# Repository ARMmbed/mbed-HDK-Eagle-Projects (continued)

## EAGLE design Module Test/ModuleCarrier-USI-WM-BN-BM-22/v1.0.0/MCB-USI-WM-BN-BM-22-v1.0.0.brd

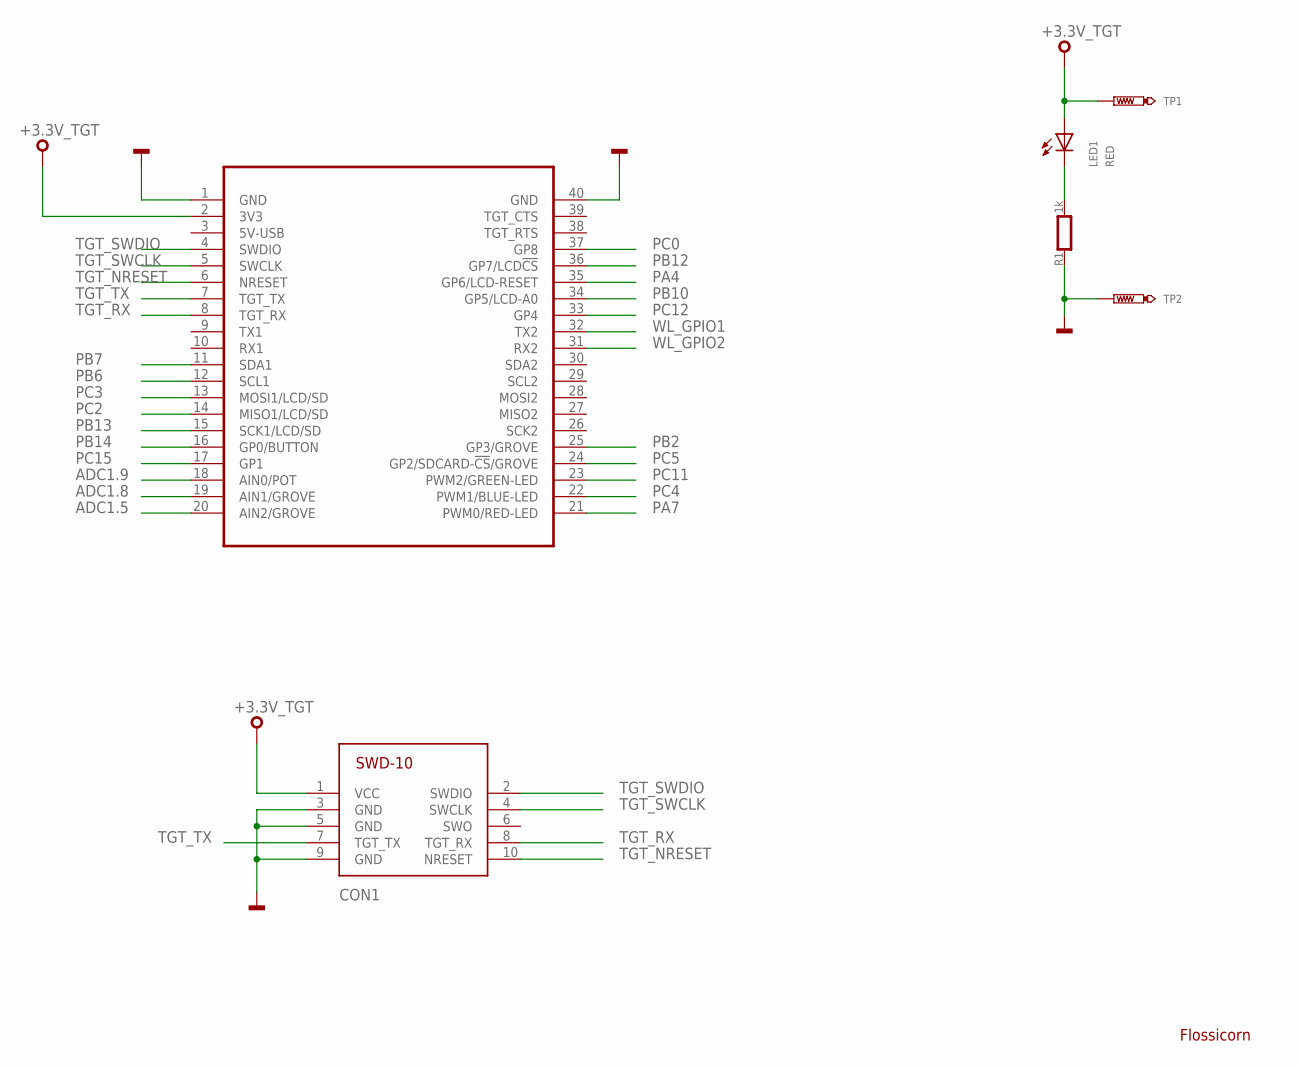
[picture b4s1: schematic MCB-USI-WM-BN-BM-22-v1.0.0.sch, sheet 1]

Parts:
CON1: SWD-10/TC2050_SMD; FTSH-105-02
LED1: RED; CHIPLED_0603
MOD1: MODULE_DAUGHTER
R1: 1k; 0603
SS1: FLOSSICORN0.5; FLOSSICORN-0.5
TP1, TP2: TEST-POINT-50R-PTH; TP50-PTH

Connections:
+3.3V_TGT: CON1.1 (VCC), LED1.A, MOD1.2 (3V3), TP1.TP; also elsewhere on the board
ADC1.5: MOD1.20 (AIN2/GROVE); also elsewhere on the board
ADC1.8: MOD1.19 (AIN1/GROVE); also elsewhere on the board
ADC1.9: MOD1.18 (AIN0/POT); also elsewhere on the board
GND: CON1.3 (GND), CON1.5 (GND), CON1.9 (GND), MOD1.1 (GND), MOD1.40 (GND), R1.1, TP2.TP; also elsewhere on the board
PA4: MOD1.35 (GP6/LCD-RESET); also elsewhere on the board
PA7: MOD1.21 (PWM0/RED-LED); also elsewhere on the board
PA_1: LED1.C, R1.2
PB2: MOD1.25 (GP3/GROVE); also elsewhere on the board
PB6: MOD1.12 (SCL1); also elsewhere on the board
PB7: MOD1.11 (SDA1); also elsewhere on the board
PB10: MOD1.34 (GP5/LCD-A0); also elsewhere on the board
PB12: MOD1.36 (GP7/LCD!CS); also elsewhere on the board
PB13: MOD1.15 (SCK1/LCD/SD); also elsewhere on the board
PB14: MOD1.16 (GP0/BUTTON); also elsewhere on the board
PC0: MOD1.37 (GP8); also elsewhere on the board
PC2: MOD1.14 (MISO1/LCD/SD); also elsewhere on the board
PC3: MOD1.13 (MOSI1/LCD/SD); also elsewhere on the board
PC4: MOD1.22 (PWM1/BLUE-LED); also elsewhere on the board
PC5: MOD1.24 (GP2/SDCARD-!CS!/GROVE); also elsewhere on the board
PC11: MOD1.23 (PWM2/GREEN-LED); also elsewhere on the board
PC12: MOD1.33 (GP4); also elsewhere on the board
PC15: MOD1.17 (GP1); also elsewhere on the board
TGT_NRESET: CON1.10 (NRESET), MOD1.6 (NRESET); also elsewhere on the board
TGT_RX: CON1.8 (TGT_RX), MOD1.8 (TGT_RX); also elsewhere on the board
TGT_SWCLK: CON1.4 (SWCLK), MOD1.5 (SWCLK); also elsewhere on the board
TGT_SWDIO: CON1.2 (SWDIO), MOD1.4 (SWDIO); also elsewhere on the board
TGT_TX: CON1.7 (TGT_TX), MOD1.7 (TGT_TX); also elsewhere on the board
WL_GPIO1: MOD1.32 (TX2); also elsewhere on the board
WL_GPIO2: MOD1.31 (RX2); also elsewhere on the board

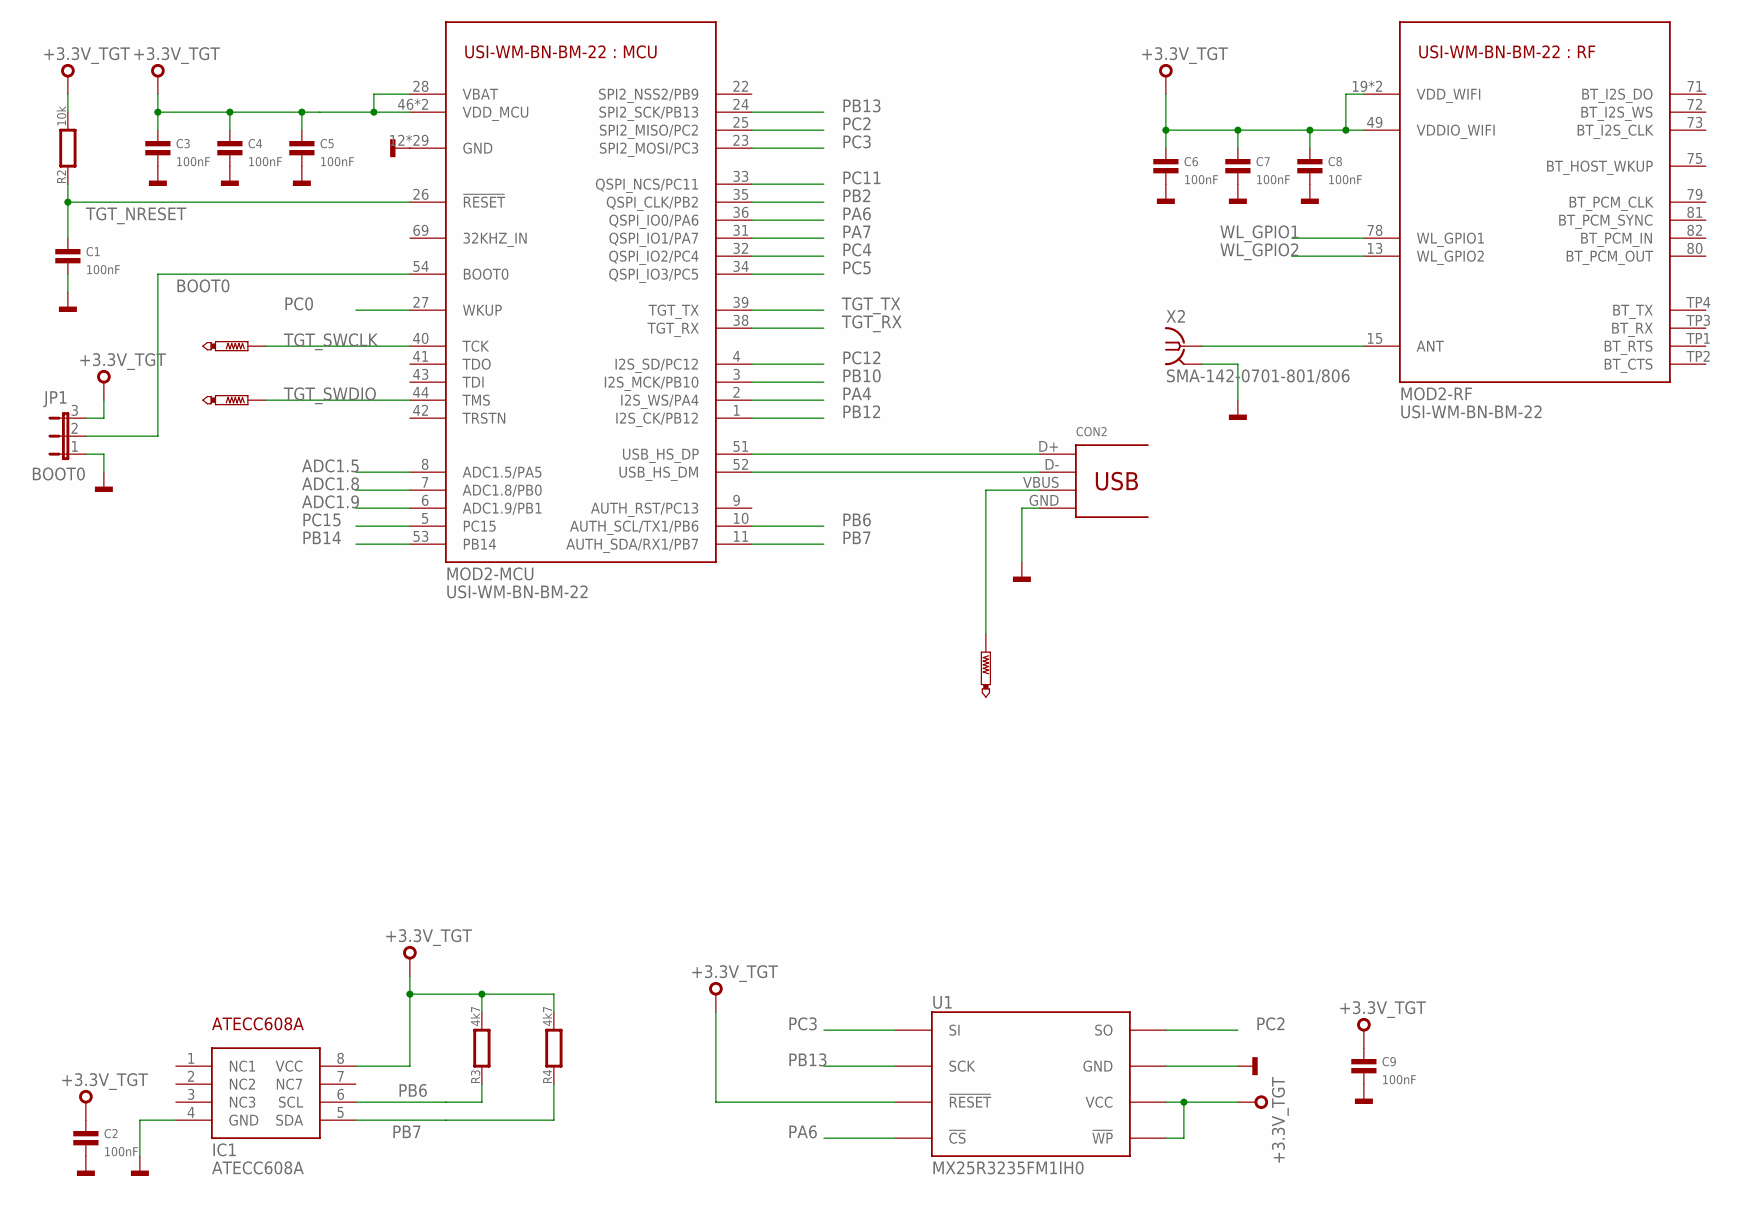
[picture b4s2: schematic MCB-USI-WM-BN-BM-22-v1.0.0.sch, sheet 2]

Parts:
C1, C2, C3, C4, C5, C6, C7, C8, C9: 100nF; 0603
CON2: 47346-0001; USB-MICRO-B-H
IC1: ATECC608A; SO8
JP1: BOOT0; JP2
MOD2: USI-WM-BN-BM-22
R2: 10k; 0603
R3, R4: 4k7; 0603
TP3, TP4: PTR1TP10R; TP10R
TP5: PTR1TP07R; TP07R
U1: MX25R3235FM1IH0; SO8
X2: SMA-142-0701-801/806; J502-ND-142-0701-801/806

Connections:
+3.3V_TGT: C2.1, C3.1, C4.1, C5.1, C6.1, C7.1, C8.1, C9.1, IC1.8 (VCC), JP1.3, MOD2.19 (VDD_WIFI), MOD2.20 (VDD_WIFI), MOD2.28 (VBAT), MOD2.46 (VDD_MCU), MOD2.47 (VDD_MCU), MOD2.49 (VDDIO_WIFI), R2.2, R3.2, R4.2, U1.3 (!WP), U1.7 (!RESET), U1.8 (VCC); also elsewhere on the board
ADC1.5: MOD2.8 (ADC1.5/PA5); also elsewhere on the board
ADC1.8: MOD2.7 (ADC1.8/PB0); also elsewhere on the board
ADC1.9: MOD2.6 (ADC1.9/PB1); also elsewhere on the board
BOOT0: JP1.2, MOD2.54 (BOOT0)
GND: C1.2, C2.2, C3.2, C4.2, C5.2, C6.2, C7.2, C8.2, C9.2, CON2.GND, IC1.4 (GND), JP1.1, MOD2.12 (GND), MOD2.14 (GND), MOD2.16 (GND), MOD2.17 (GND), MOD2.18 (GND), MOD2.21 (GND), MOD2.29 (GND), MOD2.30 (GND), MOD2.37 (GND), MOD2.45 (GND), MOD2.48 (GND), MOD2.50 (GND), MOD2.55 (GND), MOD2.56 (GND), MOD2.57 (GND), MOD2.58 (GND), MOD2.59 (GND), MOD2.60 (GND), MOD2.61 (GND), MOD2.62 (GND), MOD2.63 (GND), MOD2.64 (GND), MOD2.65 (GND), MOD2.66 (GND), MOD2.67 (GND), MOD2.68 (GND), MOD2.70 (GND), MOD2.74 (GND), MOD2.83 (GND), U1.4 (GND), X2.G@1 (2), X2.G@2 (2), X2.G@3 (2), X2.G@4 (2); also elsewhere on the board
unnamed: CON2.D+, MOD2.51 (USB_HS_DP)
unnamed: CON2.D-, MOD2.52 (USB_HS_DM)
unnamed: CON2.VBUS, TP5.TP
unnamed: MOD2.15 (ANT), X2.1
PA4: MOD2.2 (I2S_WS/PA4); also elsewhere on the board
PA6: MOD2.36 (QSPI_IO0/PA6), U1.1 (!CS)
PA7: MOD2.31 (QSPI_IO1/PA7); also elsewhere on the board
PB2: MOD2.35 (QSPI_CLK/PB2); also elsewhere on the board
PB6: IC1.6 (SCL), MOD2.10 (AUTH_SCL/TX1/PB6), R3.1; also elsewhere on the board
PB7: IC1.5 (SDA), MOD2.11 (AUTH_SDA/RX1/PB7), R4.1; also elsewhere on the board
PB10: MOD2.3 (I2S_MCK/PB10); also elsewhere on the board
PB12: MOD2.1 (I2S_CK/PB12); also elsewhere on the board
PB13: MOD2.24 (SPI2_SCK/PB13), U1.6 (SCK); also elsewhere on the board
PB14: MOD2.53 (PB14); also elsewhere on the board
PC0: MOD2.27 (WKUP); also elsewhere on the board
PC2: MOD2.25 (SPI2_MISO/PC2), U1.2 (SO); also elsewhere on the board
PC3: MOD2.23 (SPI2_MOSI/PC3), U1.5 (SI); also elsewhere on the board
PC4: MOD2.32 (QSPI_IO2/PC4); also elsewhere on the board
PC5: MOD2.34 (QSPI_IO3/PC5); also elsewhere on the board
PC11: MOD2.33 (QSPI_NCS/PC11); also elsewhere on the board
PC12: MOD2.4 (I2S_SD/PC12); also elsewhere on the board
PC15: MOD2.5 (PC15); also elsewhere on the board
TGT_NRESET: C1.1, MOD2.26 (!RESET), R2.1; also elsewhere on the board
TGT_RX: MOD2.38 (TGT_RX); also elsewhere on the board
TGT_SWCLK: MOD2.40 (TCK), TP4.TP; also elsewhere on the board
TGT_SWDIO: MOD2.44 (TMS), TP3.TP; also elsewhere on the board
TGT_TX: MOD2.39 (TGT_TX); also elsewhere on the board
WL_GPIO1: MOD2.78 (WL_GPIO1); also elsewhere on the board
WL_GPIO2: MOD2.13 (WL_GPIO2); also elsewhere on the board

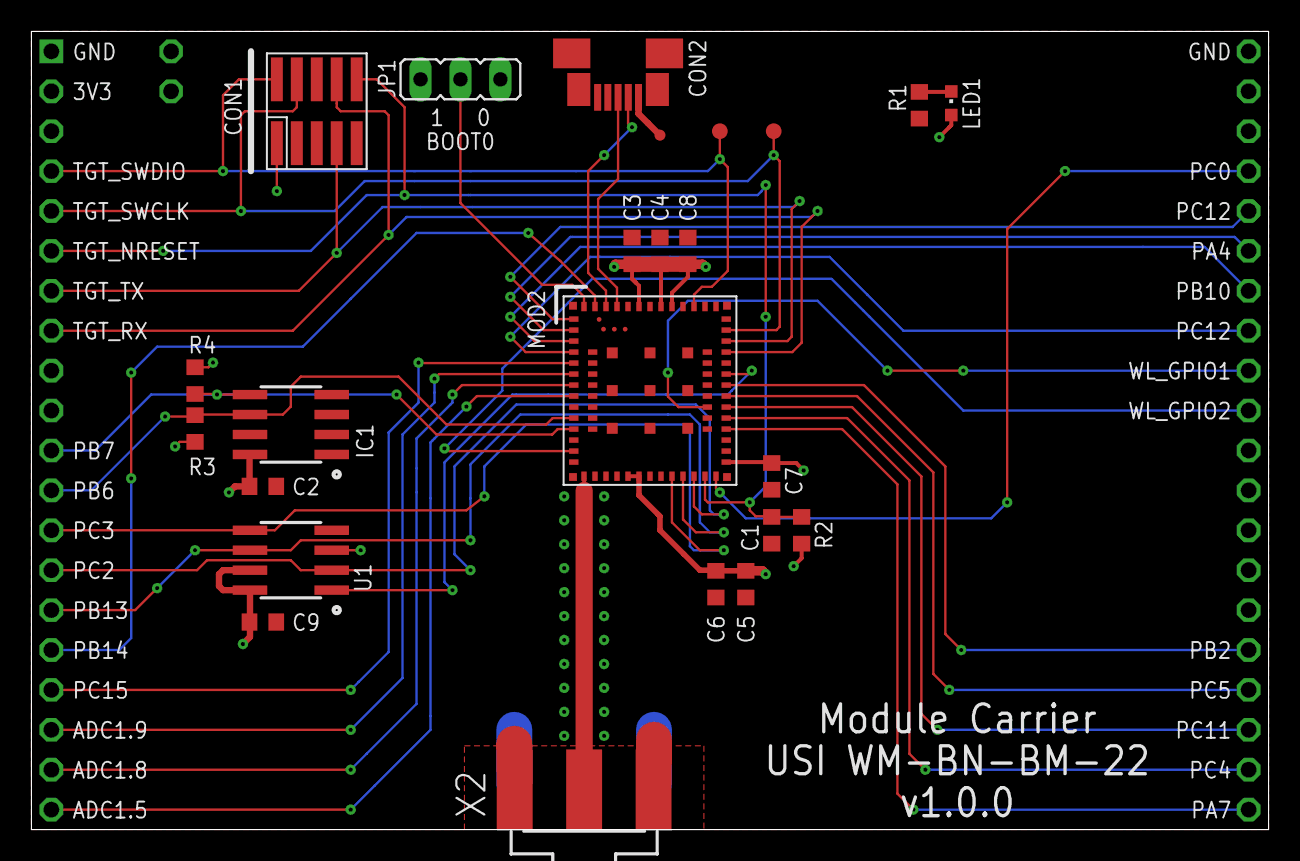
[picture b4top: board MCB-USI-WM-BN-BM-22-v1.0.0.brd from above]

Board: 2 copper layers, 78.7 x 50.8 mm, 28 parts (0 on the bottom side), 36 nets.

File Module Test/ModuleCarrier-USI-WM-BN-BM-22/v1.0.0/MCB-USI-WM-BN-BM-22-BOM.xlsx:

Qty | Value | Device | Package | Parts | Description
9 | 100nF | CAPACITOR0603 | 0603 | C1, C2, C3, C4, C5, C6, C7, C8, C9 | Capacitor
1 | 10k | RESISTOR0603 | 0603 | R2 | Resistor
1 | 1k | RESISTOR0603 | 0603 | R1 | Resistor
1 | 47346-0001 | 47346-0001 | USB-MICRO-B-H | CON2 | USB Receptacle Horizontal Micro Type B
2 | 4k7 | RESISTOR0603 | 0603 | R3, R4 | Resistor
1 | ATECC608A | ATECC608A | SO8 | IC1
1 | BOOT0 | JP2E | JP2 | JP1 | JUMPER
1 | MX25R3235FM1IH0 | MX25R3235FM1IH0 | SO8 | U1 | Serial Flash 32 Mb 80 Mhz
1 | RED | SMD_LED0603 | CHIPLED_0603 | LED1 | LED SMD, Colour Red
1 | SMA-142-0701-801/806 | SMA-142-0701-801/806 | J502-ND-142-0701-801/806 | X2 | SMA 50 Ohm End Launch Jack Receptacle
1 | USI-WM-BN-BM-22 | USI-WM-BN-BM-22 | USI-WM-BN-BM-22 | MOD2

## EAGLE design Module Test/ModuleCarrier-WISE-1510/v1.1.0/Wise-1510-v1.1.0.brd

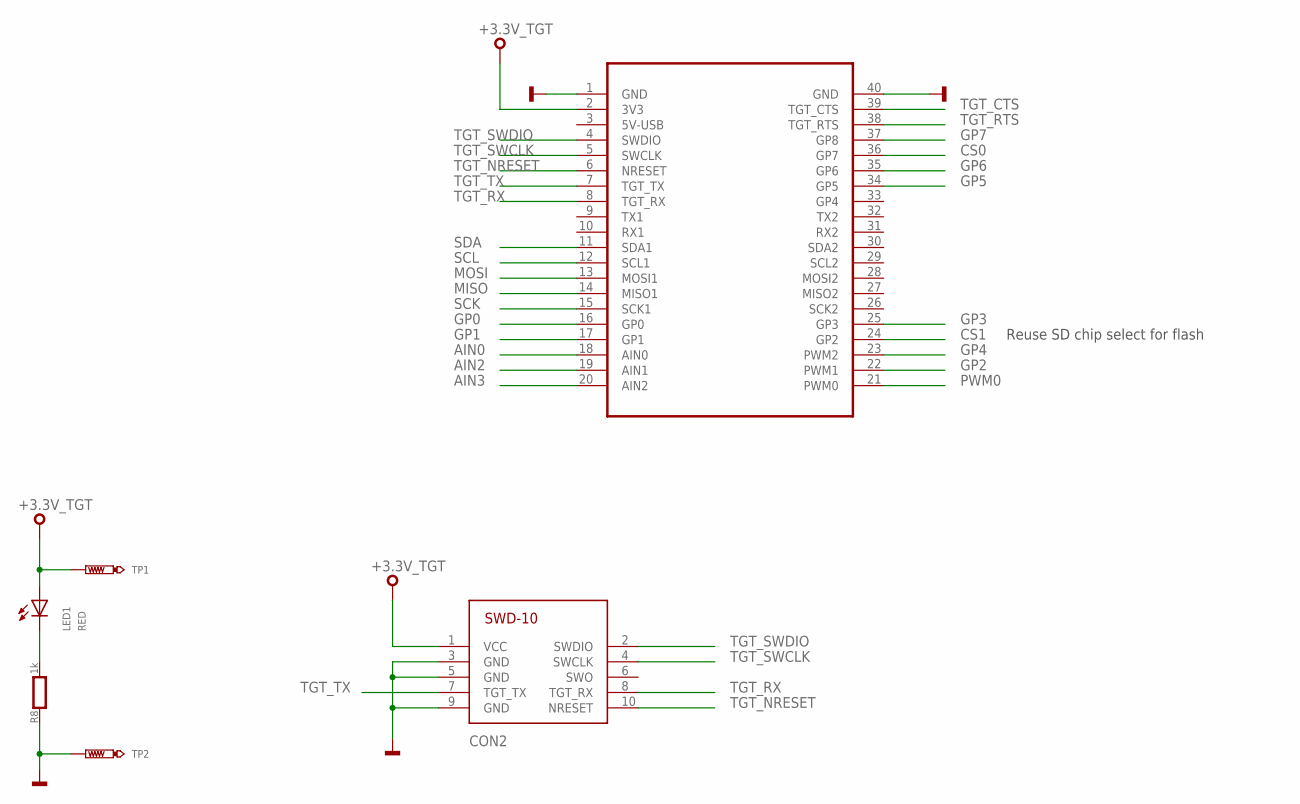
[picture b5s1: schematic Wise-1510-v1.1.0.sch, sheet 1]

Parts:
CON2: SWD-10/TC2050_SMD; FTSH-105-02
LED1: RED; CHIPLED_0603
R8: 1k; 0603
TP1, TP2: TEST-POINT-50R-PTH; TP50-PTH
U$1: MODULE_DAUGHTER

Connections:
+3.3V_TGT: CON2.1 (VCC), LED1.A, TP1.TP, U$1.2 (3V3); also elsewhere on the board
AIN0: U$1.18 (AIN0); also elsewhere on the board
AIN2: U$1.19 (AIN1); also elsewhere on the board
AIN3: U$1.20 (AIN2); also elsewhere on the board
CS0: U$1.36 (GP7); also elsewhere on the board
CS1: U$1.24 (GP2); also elsewhere on the board
GND: CON2.3 (GND), CON2.5 (GND), CON2.9 (GND), R8.1, TP2.TP, U$1.1 (GND), U$1.40 (GND); also elsewhere on the board
GP0: U$1.16 (GP0); also elsewhere on the board
GP1: U$1.17 (GP1); also elsewhere on the board
GP2: U$1.22 (PWM1); also elsewhere on the board
GP3: U$1.25 (GP3); also elsewhere on the board
GP4: U$1.23 (PWM2); also elsewhere on the board
GP5: U$1.34 (GP5); also elsewhere on the board
GP6: U$1.35 (GP6); also elsewhere on the board
GP7: U$1.37 (GP8); also elsewhere on the board
MISO: U$1.14 (MISO1); also elsewhere on the board
MOSI: U$1.13 (MOSI1); also elsewhere on the board
PA_1: LED1.C, R8.2
PWM0: U$1.21 (PWM0); also elsewhere on the board
SCK: U$1.15 (SCK1); also elsewhere on the board
SCL: U$1.12 (SCL1); also elsewhere on the board
SDA: U$1.11 (SDA1); also elsewhere on the board
TGT_CTS: U$1.39 (TGT_CTS); also elsewhere on the board
TGT_NRESET: CON2.10 (NRESET), U$1.6 (NRESET); also elsewhere on the board
TGT_RTS: U$1.38 (TGT_RTS); also elsewhere on the board
TGT_RX: CON2.8 (TGT_RX), U$1.8 (TGT_RX); also elsewhere on the board
TGT_SWCLK: CON2.4 (SWCLK), U$1.5 (SWCLK); also elsewhere on the board
TGT_SWDIO: CON2.2 (SWDIO), U$1.4 (SWDIO); also elsewhere on the board
TGT_TX: CON2.7 (TGT_TX), U$1.7 (TGT_TX); also elsewhere on the board

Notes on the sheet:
Reuse SD chip select for flash

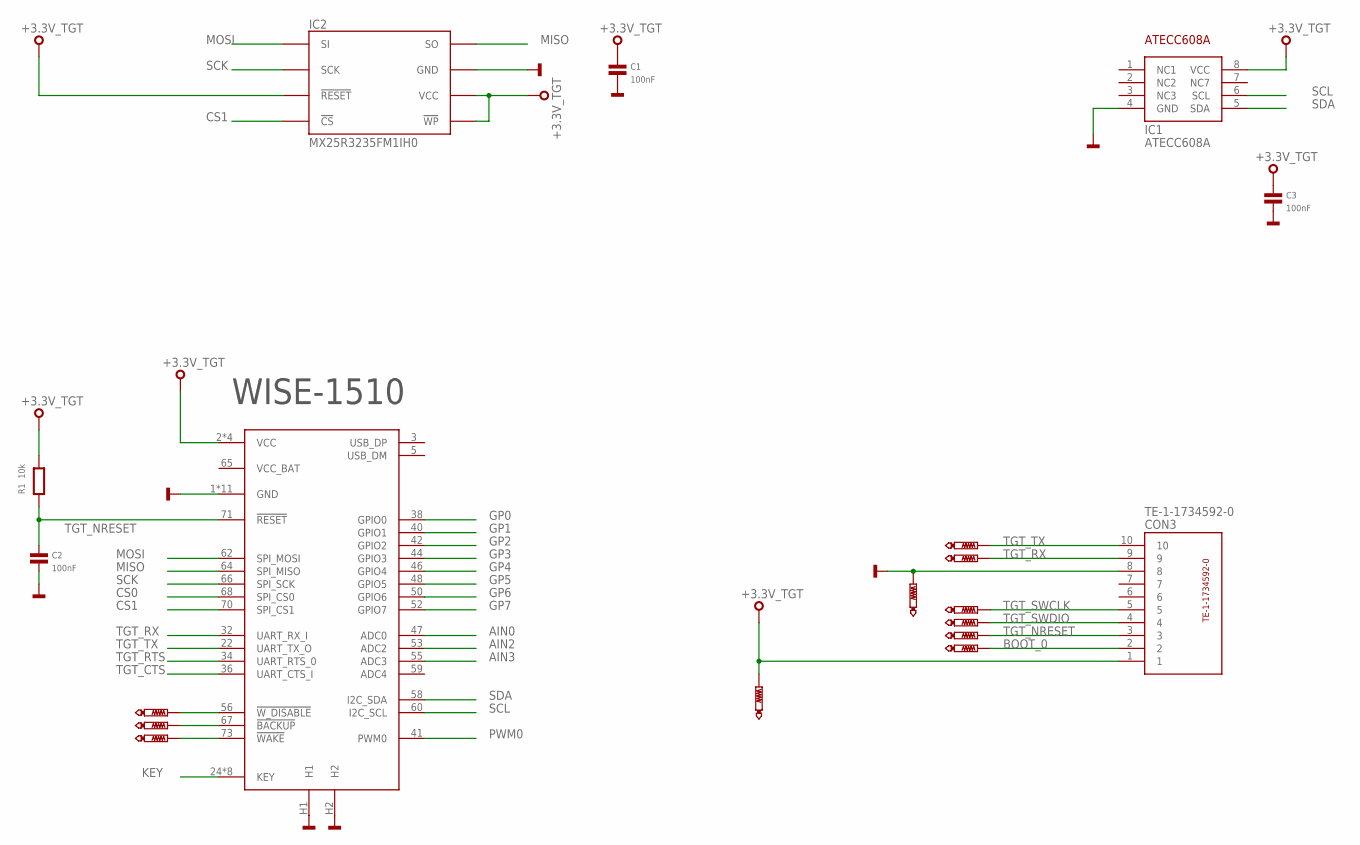
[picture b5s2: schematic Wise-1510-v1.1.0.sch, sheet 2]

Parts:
C1, C2, C3: 100nF; 0603
CON1: WISE-1510_E; MDT420E02001
CON3: TE-1-1734592-0
IC1: ATECC608A; SO8
IC2: MX25R3235FM1IH0; SO8
R1: 10k; 0603
TP3, TP4, TP5, TP6, TP7, TP8, TP12, TP13: PTR1TP08R; TP08R
TP9, TP10, TP11: PTR1B1,27; B1,27

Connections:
+3.3V_TGT: C1.1, C3.1, CON1.2 (VCC), CON1.4 (VCC), CON1.72 (VCC), CON1.74 (VCC), CON3.1, IC1.8 (VCC), IC2.3 (!WP), IC2.7 (!RESET), IC2.8 (VCC), R1.2, TP12.TP; also elsewhere on the board
AIN0: CON1.47 (ADC0); also elsewhere on the board
AIN2: CON1.53 (ADC2); also elsewhere on the board
AIN3: CON1.55 (ADC3); also elsewhere on the board
BOOT_0: CON3.2, TP8.TP
CS0: CON1.68 (SPI_CS0); also elsewhere on the board
CS1: CON1.70 (SPI_CS1), IC2.1 (!CS); also elsewhere on the board
GND: C1.2, C2.2, C3.2, CON1.1 (GND), CON1.7 (GND), CON1.18 (GND), CON1.33 (GND), CON1.39 (GND), CON1.45 (GND), CON1.51 (GND), CON1.57 (GND), CON1.63 (GND), CON1.69 (GND), CON1.75 (GND), CON1.H1, CON1.H2, CON3.8, IC1.4 (GND), IC2.4 (GND), TP13.TP; also elsewhere on the board
GP0: CON1.38 (GPIO0); also elsewhere on the board
GP1: CON1.40 (GPIO1); also elsewhere on the board
GP2: CON1.42 (GPIO2); also elsewhere on the board
GP3: CON1.44 (GPIO3); also elsewhere on the board
GP4: CON1.46 (GPIO4); also elsewhere on the board
GP5: CON1.48 (GPIO5); also elsewhere on the board
GP6: CON1.50 (GPIO6); also elsewhere on the board
GP7: CON1.52 (GPIO7); also elsewhere on the board
KEY: CON1.24 (KEY), CON1.25 (KEY), CON1.26 (KEY), CON1.27 (KEY), CON1.28 (KEY), CON1.29 (KEY), CON1.30 (KEY), CON1.31 (KEY)
MISO: CON1.64 (SPI_MISO), IC2.2 (SO); also elsewhere on the board
MOSI: CON1.62 (SPI_MOSI), IC2.5 (SI); also elsewhere on the board
unnamed: CON1.56 (!W_DISABLE), TP9.TP
unnamed: CON1.67 (!BACKUP), TP10.TP
unnamed: CON1.73 (!WAKE), TP11.TP
PWM0: CON1.41 (PWM0); also elsewhere on the board
SCK: CON1.66 (SPI_SCK), IC2.6 (SCK); also elsewhere on the board
SCL: CON1.60 (I2C_SCL), IC1.6 (SCL); also elsewhere on the board
SDA: CON1.58 (I2C_SDA), IC1.5 (SDA); also elsewhere on the board
TGT_CTS: CON1.36 (UART_CTS_I); also elsewhere on the board
TGT_NRESET: C2.1, CON1.71 (!RESET), CON3.3, R1.1, TP5.TP; also elsewhere on the board
TGT_RTS: CON1.34 (UART_RTS_0); also elsewhere on the board
TGT_RX: CON1.32 (UART_RX_I), CON3.9, TP6.TP; also elsewhere on the board
TGT_SWCLK: CON3.5, TP3.TP; also elsewhere on the board
TGT_SWDIO: CON3.4, TP4.TP; also elsewhere on the board
TGT_TX: CON1.22 (UART_TX_O), CON3.10, TP7.TP; also elsewhere on the board

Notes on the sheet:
WISE-1510

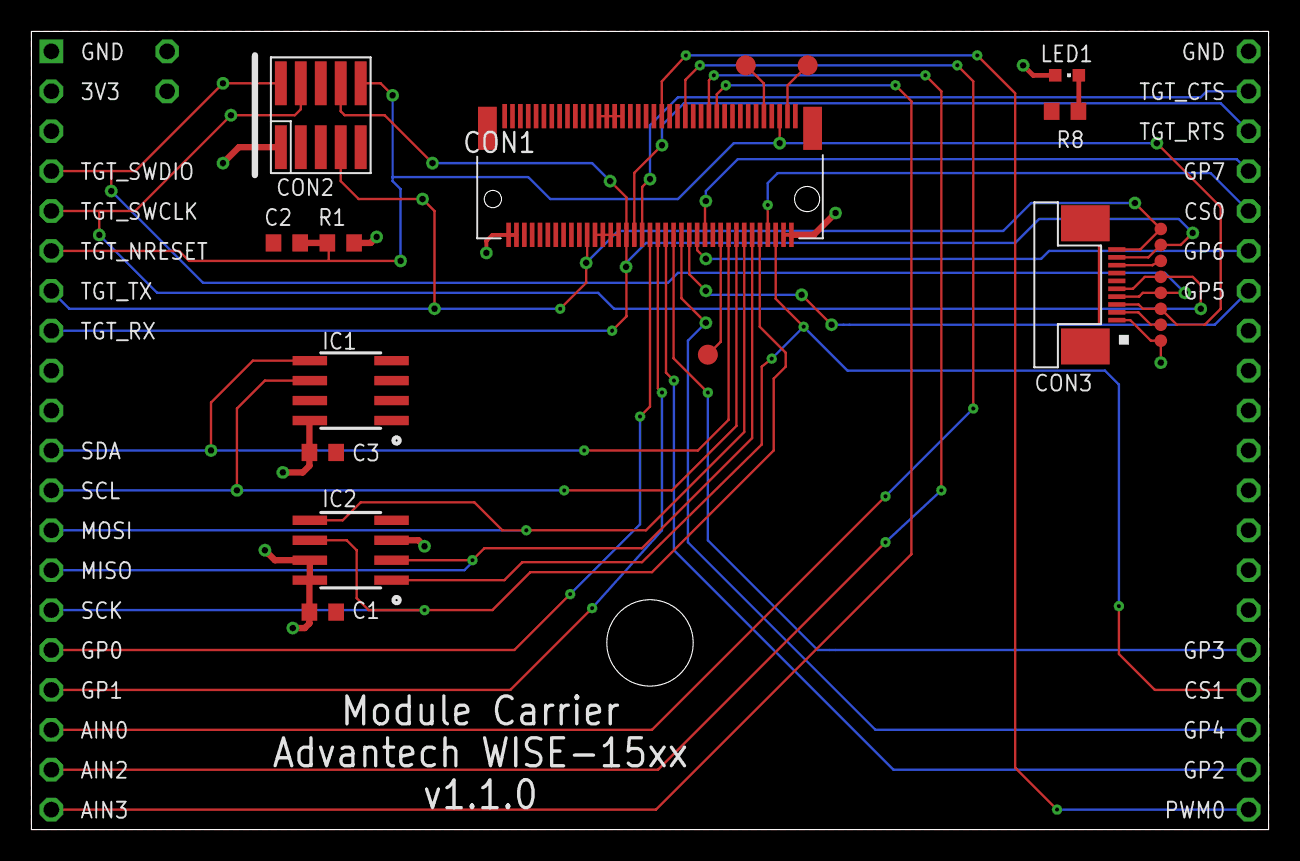
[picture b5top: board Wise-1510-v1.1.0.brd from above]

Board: 2 copper layers, 78.7 x 50.8 mm, 25 parts (0 on the bottom side), 34 nets.

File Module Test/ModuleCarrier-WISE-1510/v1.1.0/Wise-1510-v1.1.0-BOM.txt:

Partlist exported from C:/Users/cstyles/Documents/mbed/Projects/blackbriar/ModuleCarrier-WISE-1510/v1.1.0/Wise-1510-v1.1.0.sch at 18/12/2017 01:39

Qty Value              Device             Package         Parts                                    Description                                                                                          
3   100nF              CAPACITOR0603      0603            C1, C2, C3                               Capacitor                                                                                            
1   10k                RESISTOR0603       0603            R1                                       Resistor                                                                                             
1   1k                 RESISTOR0603       0603            R8                                       Resistor                                                                                             
1   ATECC608A          ATECC608A          SO8             IC1                                                                                                                                           
1   MODULE_DAUGHTER    MODULE_DAUGHTER    MODULE_DAUGHTER U$1                                                                                                                                           
1   MX25R3235FM1IH0    MX25R3235FM1IH0    SO8             IC2                                      Serial Flash 32 Mb 80 Mhz                                                                            
3   PTR1B1,27          PTR1B1,27          B1,27           TP9, TP10, TP11                          TEST PIN                                                                                             
8   PTR1TP08R          PTR1TP08R          TP08R           TP3, TP4, TP5, TP6, TP7, TP8, TP12, TP13 TEST PIN                                                                                             
1   RED                SMD_LED0603        CHIPLED_0603    LED1                                     LED SMD, Colour Red                                                                                  
1   SWD-10/TC2050_SMD  SWD-10/TC2050_SMD  FTSH-105-02     CON2                                     1mm pitch 10-Pin Cortex Programming Header with optional TC2050 footprint solderless interchangeable 
1   TE-1-1734592-0     TE-1-1734592-0     TE-1-1734592-0  CON3                                                                                                                                          
2   TEST-POINT-50R-PTH TEST-POINT-50R-PTH TP50-PTH        TP1, TP2                                                                                                                                      
1   WISE-1510_E        WISE-1510_E        MDT420E02001    CON1

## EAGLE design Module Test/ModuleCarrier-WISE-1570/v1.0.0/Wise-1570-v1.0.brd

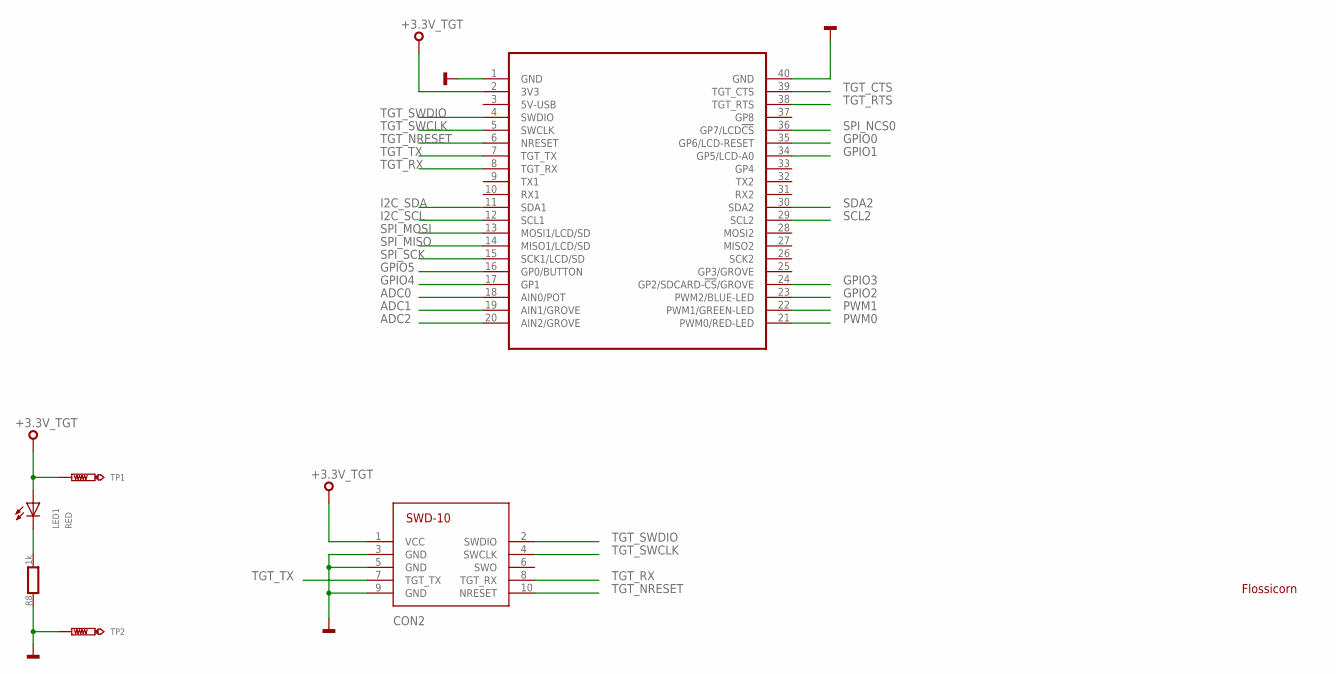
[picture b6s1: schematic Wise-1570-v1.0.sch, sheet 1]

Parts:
CON2: SWD-10/TC2050_SMD; FTSH-105-02
LED1: RED; CHIPLED_0603
MOD2: MODULE_DAUGHTER
R8: 1k; 0603
SS1: FLOSSICORN0.25; FLOSSICORN-0.25
TP1, TP2: TEST-POINT-50R-PTH; TP50-PTH

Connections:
+3.3V_TGT: CON2.1 (VCC), LED1.A, MOD2.2 (3V3), TP1.TP; also elsewhere on the board
ADC0: MOD2.18 (AIN0/POT); also elsewhere on the board
ADC1: MOD2.19 (AIN1/GROVE); also elsewhere on the board
ADC2: MOD2.20 (AIN2/GROVE); also elsewhere on the board
GND: CON2.3 (GND), CON2.5 (GND), CON2.9 (GND), MOD2.1 (GND), MOD2.40 (GND), R8.1, TP2.TP; also elsewhere on the board
GPIO0: MOD2.35 (GP6/LCD-RESET); also elsewhere on the board
GPIO1: MOD2.34 (GP5/LCD-A0); also elsewhere on the board
GPIO2: MOD2.23 (PWM2/BLUE-LED); also elsewhere on the board
GPIO3: MOD2.24 (GP2/SDCARD-!CS!/GROVE); also elsewhere on the board
GPIO4: MOD2.17 (GP1); also elsewhere on the board
GPIO5: MOD2.16 (GP0/BUTTON); also elsewhere on the board
I2C_SCL: MOD2.12 (SCL1); also elsewhere on the board
I2C_SDA: MOD2.11 (SDA1); also elsewhere on the board
PA_1: LED1.C, R8.2
PWM0: MOD2.21 (PWM0/RED-LED); also elsewhere on the board
PWM1: MOD2.22 (PWM1/GREEN-LED); also elsewhere on the board
SCL2: MOD2.29 (SCL2); also elsewhere on the board
SDA2: MOD2.30 (SDA2); also elsewhere on the board
SPI_MISO: MOD2.14 (MISO1/LCD/SD); also elsewhere on the board
SPI_MOSI: MOD2.13 (MOSI1/LCD/SD); also elsewhere on the board
SPI_NCS0: MOD2.36 (GP7/LCD!CS); also elsewhere on the board
SPI_SCK: MOD2.15 (SCK1/LCD/SD); also elsewhere on the board
TGT_CTS: MOD2.39 (TGT_CTS); also elsewhere on the board
TGT_NRESET: CON2.10 (NRESET), MOD2.6 (NRESET); also elsewhere on the board
TGT_RTS: MOD2.38 (TGT_RTS); also elsewhere on the board
TGT_RX: CON2.8 (TGT_RX), MOD2.8 (TGT_RX); also elsewhere on the board
TGT_SWCLK: CON2.4 (SWCLK), MOD2.5 (SWCLK); also elsewhere on the board
TGT_SWDIO: CON2.2 (SWDIO), MOD2.4 (SWDIO); also elsewhere on the board
TGT_TX: CON2.7 (TGT_TX), MOD2.7 (TGT_TX); also elsewhere on the board

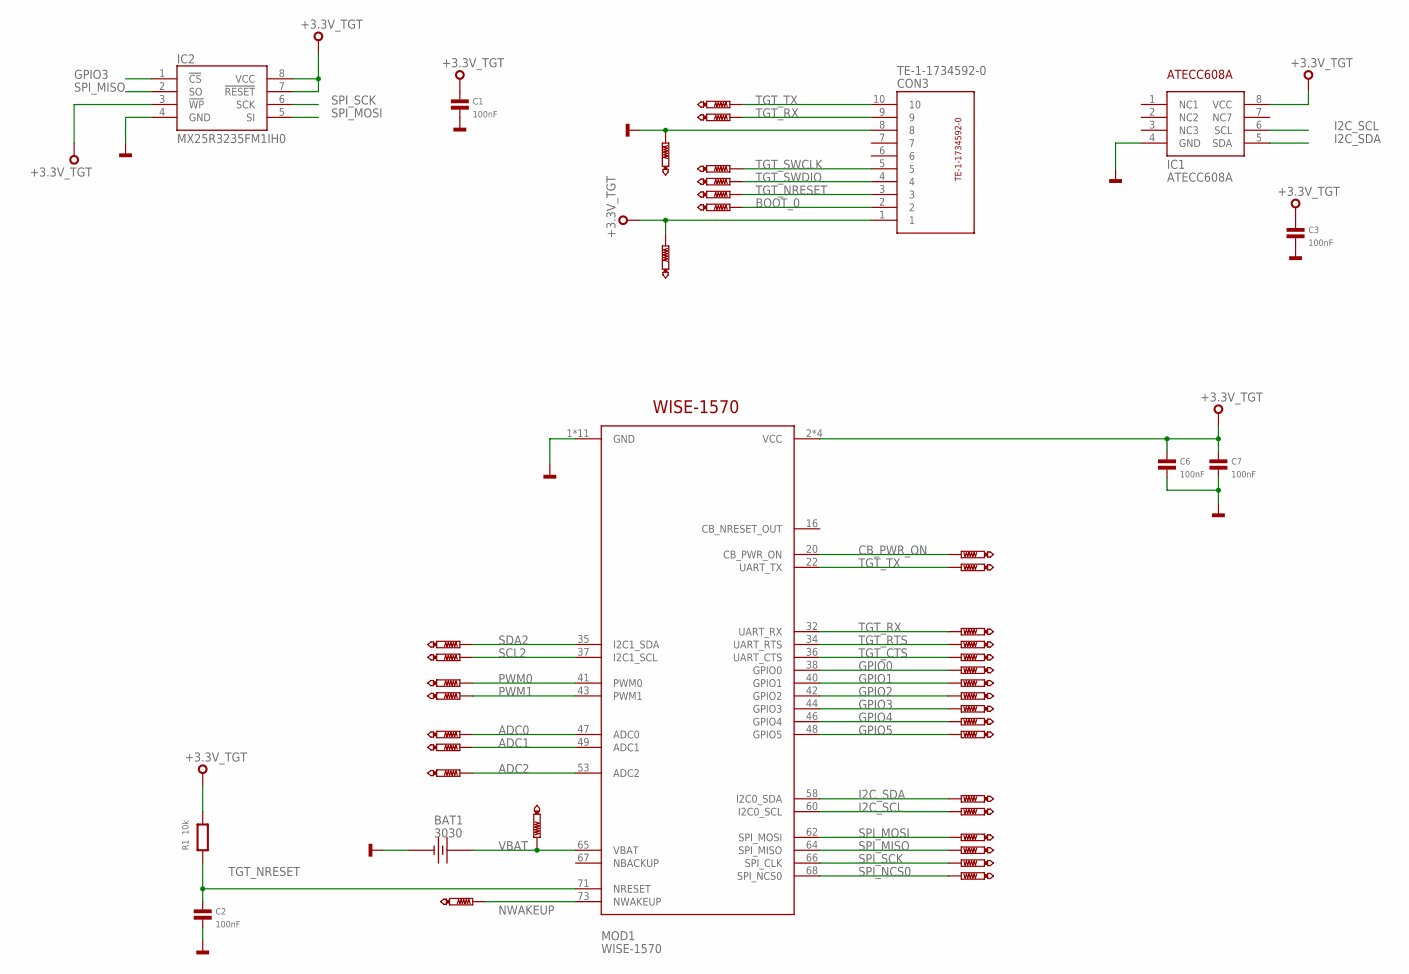
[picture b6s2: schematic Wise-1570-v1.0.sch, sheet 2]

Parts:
BAT1: 3030
C1, C2, C3, C6, C7: 100nF; 0603
CON3: TE-1-1734592-0
IC1: ATECC608A; SO8
IC2: MX25R3235FM1IH0; SO8
MOD1: WISE-1570; MDT420E02001
R1: 10k; 0603
TP3, TP4, TP5, TP6, TP7, TP8, TP12, TP13: PTR1TP08R; TP08R
TP9, TP10, TP11, TP14, TP15, TP16, TP17, TP18, TP19, TP20, TP21, TP22, TP23, TP24, TP25, TP26, TP27, TP28, TP29, TP30, TP31, TP32, TP33, TP34, TP35, TP36: PTR1TP07R; TP07R

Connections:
+3.3V_TGT: C1.1, C3.1, C6.1, C7.1, CON3.1, IC1.8 (VCC), IC2.3 (!WP), IC2.7 (!RESET), IC2.8 (VCC), MOD1.2 (VCC), MOD1.4 (VCC), MOD1.72 (VCC), MOD1.74 (VCC), R1.2, TP12.TP; also elsewhere on the board
ADC0: MOD1.47 (ADC0), TP29.TP; also elsewhere on the board
ADC1: MOD1.49 (ADC1), TP30.TP; also elsewhere on the board
ADC2: MOD1.53 (ADC2), TP31.TP; also elsewhere on the board
BOOT_0: CON3.2, TP8.TP
CB_PWR_ON: MOD1.20 (CB_PWR_ON), TP14.TP
GND: BAT1.-, C1.2, C2.2, C3.2, C6.2, C7.2, CON3.8, IC1.4 (GND), IC2.4 (GND), MOD1.1 (GND), MOD1.7 (GND), MOD1.18 (GND), MOD1.33 (GND), MOD1.39 (GND), MOD1.45 (GND), MOD1.51 (GND), MOD1.57 (GND), MOD1.63 (GND), MOD1.69 (GND), MOD1.75 (GND), TP13.TP; also elsewhere on the board
GPIO0: MOD1.38 (GPIO0), TP27.TP; also elsewhere on the board
GPIO1: MOD1.40 (GPIO1), TP26.TP; also elsewhere on the board
GPIO2: MOD1.42 (GPIO2), TP32.TP; also elsewhere on the board
GPIO3: IC2.1 (!CS), MOD1.44 (GPIO3), TP25.TP; also elsewhere on the board
GPIO4: MOD1.46 (GPIO4), TP24.TP; also elsewhere on the board
GPIO5: MOD1.48 (GPIO5), TP23.TP; also elsewhere on the board
I2C_SCL: IC1.6 (SCL), MOD1.60 (I2C0_SCL), TP20.TP; also elsewhere on the board
I2C_SDA: IC1.5 (SDA), MOD1.58 (I2C0_SDA), TP21.TP; also elsewhere on the board
NWAKEUP: MOD1.73 (NWAKEUP), TP34.TP
PWM0: MOD1.41 (PWM0), TP16.TP; also elsewhere on the board
PWM1: MOD1.43 (PWM1), TP17.TP; also elsewhere on the board
SCL2: MOD1.37 (I2C1_SCL), TP36.TP; also elsewhere on the board
SDA2: MOD1.35 (I2C1_SDA), TP35.TP; also elsewhere on the board
SPI_MISO: IC2.2 (SO), MOD1.64 (SPI_MISO), TP11.TP; also elsewhere on the board
SPI_MOSI: IC2.5 (SI), MOD1.62 (SPI_MOSI), TP22.TP; also elsewhere on the board
SPI_NCS0: MOD1.68 (SPI_NCS0), TP9.TP; also elsewhere on the board
SPI_SCK: IC2.6 (SCK), MOD1.66 (SPI_CLK), TP10.TP; also elsewhere on the board
TGT_CTS: MOD1.36 (UART_CTS), TP19.TP; also elsewhere on the board
TGT_NRESET: C2.1, CON3.3, MOD1.71 (NRESET), R1.1, TP5.TP; also elsewhere on the board
TGT_RTS: MOD1.34 (UART_RTS), TP18.TP; also elsewhere on the board
TGT_RX: CON3.9, MOD1.32 (UART_RX), TP6.TP, TP28.TP; also elsewhere on the board
TGT_SWCLK: CON3.5, TP3.TP; also elsewhere on the board
TGT_SWDIO: CON3.4, TP4.TP; also elsewhere on the board
TGT_TX: CON3.10, MOD1.22 (UART_TX), TP7.TP, TP15.TP; also elsewhere on the board
VBAT: BAT1.+1 (+), BAT1.+2 (+), MOD1.65 (VBAT), TP33.TP
